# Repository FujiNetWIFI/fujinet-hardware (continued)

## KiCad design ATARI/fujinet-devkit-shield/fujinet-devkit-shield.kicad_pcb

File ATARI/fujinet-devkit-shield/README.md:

# fujinet-devkit-shield

These files are sourced from https://github.com/djtersteegc/fujinet-devkit-shield

This is an alternative hardware platform for [FujiNet](https://fujinet.online/) that allows you to build your own using all through-hole technology (THT) components and an Espressif ESP32-DevKitC-VE devkit board.  You could probably also use a ESP32-DevKitC-VIE board, but you will need to either use an external IPEX connected antenna or engage in some micro soldering since the on-board PCB antenna is not connected by default. You must use ESP32-WROVER based devkit boards, the cheaper ESP32-WROOM boards lack the PSRAM needed by FujiNet code these days. 

The PCB is designed for flexibility in building, with different cabling options and headers for the buttons and LEDs if you want to mount this in your own enclosure. Most components are "jelly bean" parts you may already have or can be purchased for one or two cents in quantity from the usual China based suppliers.  Total cost of the build should be around $20, depending on where you source your parts.  Please see the assembly page for more details.

[Hardware Component Choices and Assembly](https://djtersteegc.github.io/fujinet-devkit-shield/assembly.html)

An interactive BOM and parts placement diagram is also available.

[Interactive Bill of Materials (BOM)](https://djtersteegc.github.io/fujinet-devkit-shield/ibom.html)

Currently this board is not supported by the FujiNet updater app so you will need to use Platform IO to build and upload your own binaries.  Build with the 8MB flash target since the devkit boards have half the flash of the 16MB WROVER modules used on the SIO mounted FujiNet designed by [mozzwald](https://github.com/mozzwald).  In normal operation is should not really matter since 6MB in the 16MB version is currently reserved for over the air (OTA) updates and the release build uses a little more than 2MB of flash as of March 2021 so lots of free space still for future development.

[Board bring up for FujiNet Platform.IO code](https://github.com/FujiNetWIFI/fujinet-platformio/wiki/Board-bring-up-for-FujiNet-Platform.IO-code)

STL's and the [DesignSpark Mechanical](https://www.rs-online.com/designspark/mechanical-software) source file for a 3D printable enclosure are in the **enclosure** directory. Assemble with four M3x10mm screws. Make sure to print 3 copies of the button file.

# Getting a Board

If I have extra PCB's, they will be listed on Tindie.

[https://www.tindie.com/products/tersteeg/fujinet-devkit-shield/](https://www.tindie.com/products/tersteeg/fujinet-devkit-shield/)

Otherwise you can download the Gerbers and use your favorite fab (JLCPCB, PCBWay, etc.) to make your own batch.  It's a standard two layer, 1oz copper board with dimensions of 99mm x 56mm so it squeaks under the 100mm x 100mm limit of the cheap Chinese fabs.

# Hardware Revisions

### Version 1.0

Mostly tested. Standard pin header cable with the SMD MicroSD card connector works.  Still waiting for DB15 connectors to test that cable configuration and a 4.7uf ceramic cap for audio in line. Will also build that one with the micro SD breakout board to verify.  External pin headers for the buttons and LEDs are also untested, but should work. Equivalent to version 1.3+ (pull-up resistors on the SIO and SD card lines) of the SIO port mounted FujiNet.

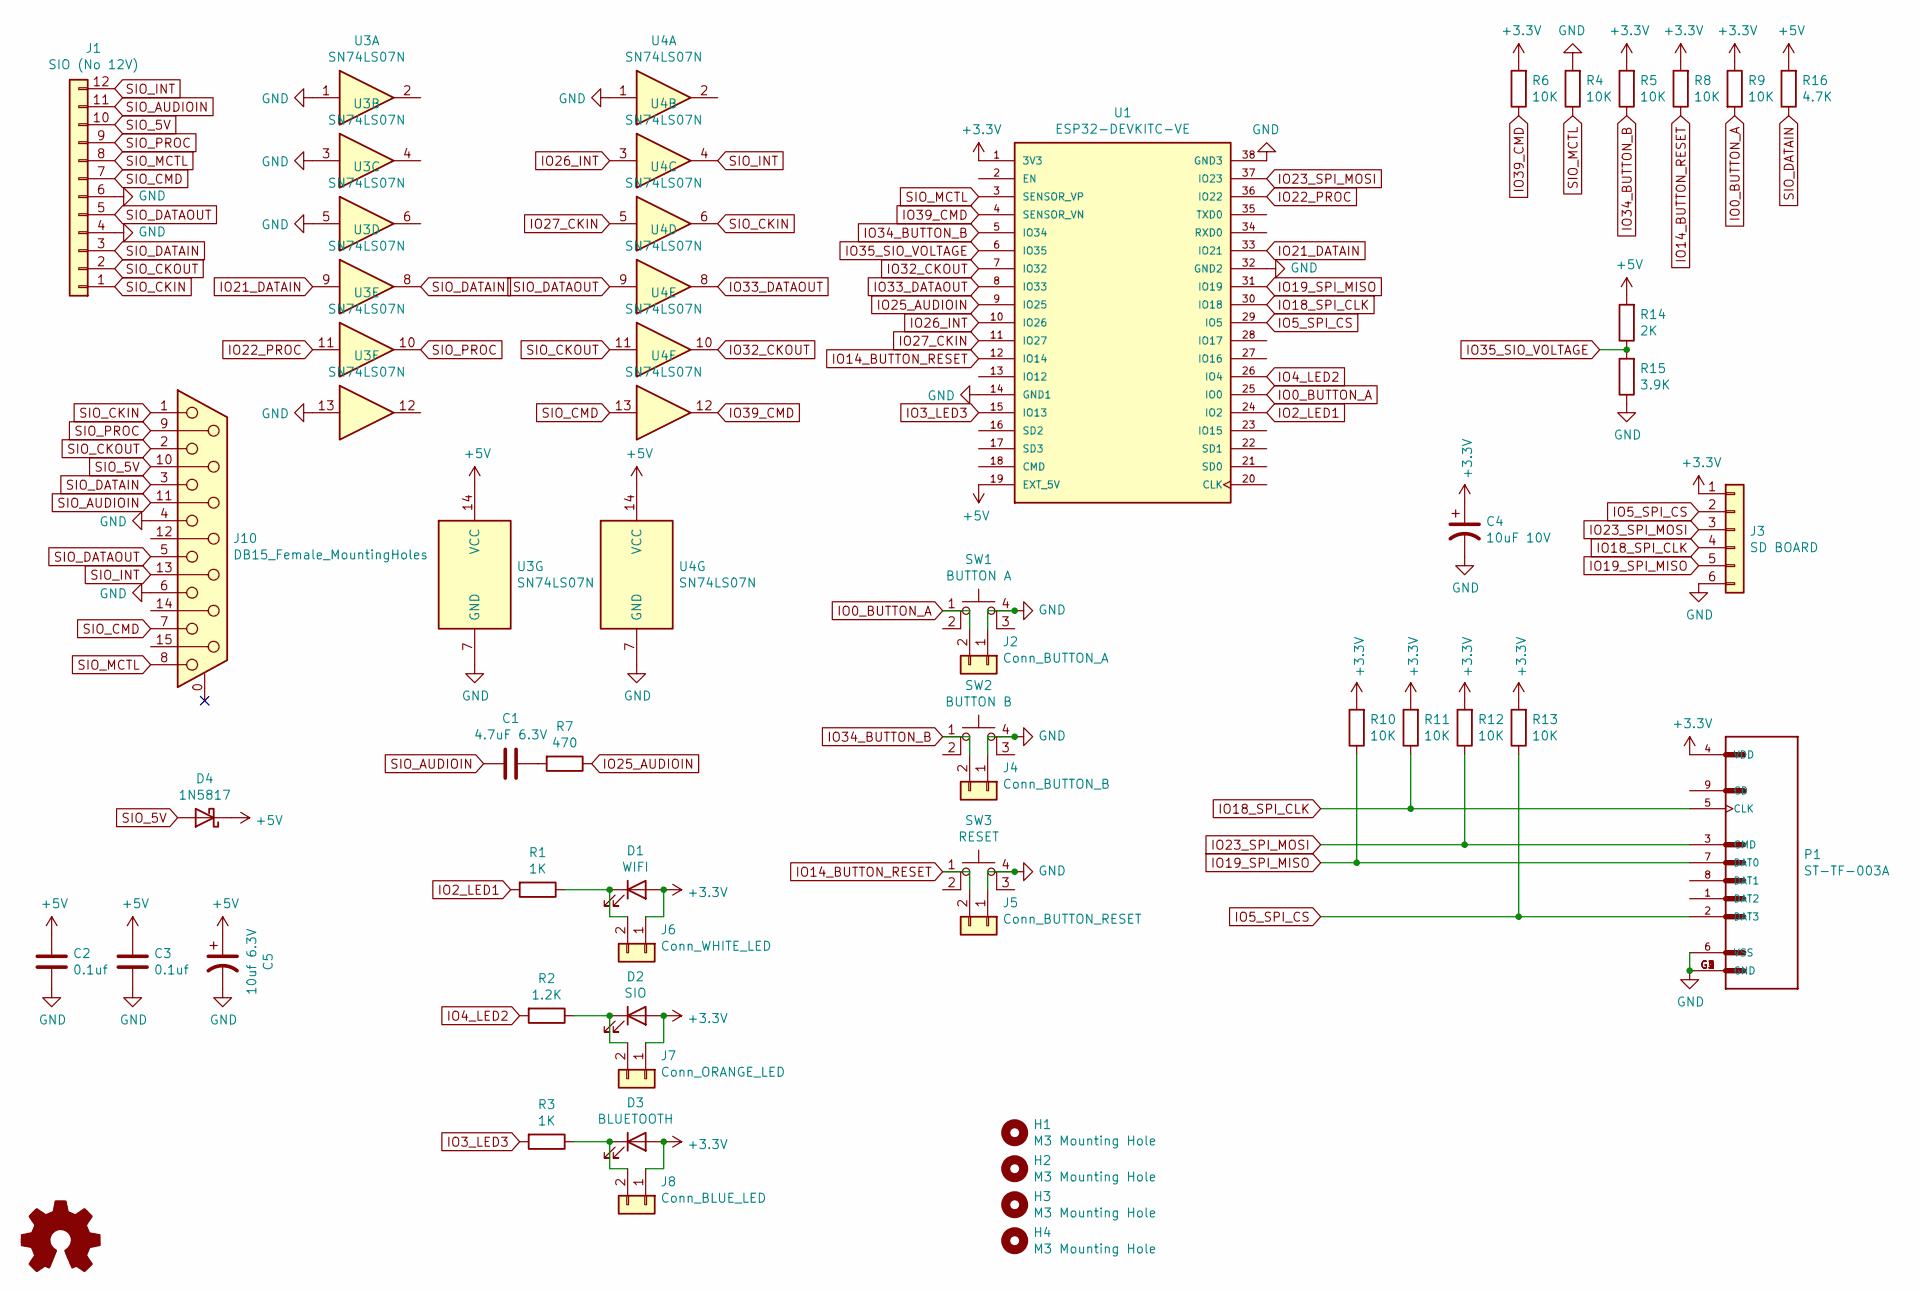
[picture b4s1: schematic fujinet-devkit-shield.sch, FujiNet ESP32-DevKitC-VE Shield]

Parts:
C1: 4.7uF 6.3V; C_Disc_D5.1mm_W3.2mm_P5.00mm
C2, C3: 0.1uf; C_Disc_D5.0mm_W2.5mm_P5.00mm
C4: 10uF 10V; CP_Radial_Tantal_D5.5mm_P5.00mm
C5: 10uf 6.3V; CP_Radial_D6.3mm_P2.50mm
D1: WIFI; LED_D5.0mm
D2: SIO; LED_D5.0mm
D3: BLUETOOTH; LED_D5.0mm
D4: 1N5817; D_DO-41_SOD81_P10.16mm_Horizontal
H1, H2, H3, H4: M3 Mounting Hole; MountingHole_3.2mm_M3
J1: SIO (No 12V); PinHeader_1x12_P2.54mm_Vertical
J2: Conn_BUTTON_A; PinHeader_1x02_P2.54mm_Vertical
J3: SD BOARD; PinHeader_1x06_P2.54mm_Vertical
J4: Conn_BUTTON_B; PinHeader_1x02_P2.54mm_Vertical
J5: Conn_BUTTON_RESET; PinHeader_1x02_P2.54mm_Vertical
J6: Conn_WHITE_LED; PinHeader_1x02_P2.54mm_Vertical
J7: Conn_ORANGE_LED; PinHeader_1x02_P2.54mm_Vertical
J8: Conn_BLUE_LED; PinHeader_1x02_P2.54mm_Vertical
J10: DB15_Female_MountingHoles; DSUB-15_Female_Horizontal_P2.77x2.84mm_EdgePinOffset4.94mm_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
P1: ST-TF-003A; SUNTECH_ST-TF-003A
R1, R3: 1K; R_Axial_DIN0207_L6.3mm_D2.5mm_P7.62mm_Horizontal
R2: 1.2K; R_Axial_DIN0207_L6.3mm_D2.5mm_P7.62mm_Horizontal
R4, R5, R6, R8, R9, R10, R11, R12, R13: 10K; R_Axial_DIN0207_L6.3mm_D2.5mm_P7.62mm_Horizontal
R7: 470; R_Axial_DIN0207_L6.3mm_D2.5mm_P7.62mm_Horizontal
R14: 2K; R_Axial_DIN0207_L6.3mm_D2.5mm_P7.62mm_Horizontal
R15: 3.9K; R_Axial_DIN0207_L6.3mm_D2.5mm_P7.62mm_Horizontal
R16: 4.7K; R_Axial_DIN0207_L6.3mm_D2.5mm_P7.62mm_Horizontal
SW1: BUTTON A; SW_TH_Tactile_Omron_B3F-10xx
SW2: BUTTON B; SW_TH_Tactile_Omron_B3F-10xx
SW3: RESET; SW_TH_Tactile_Omron_B3F-10xx
U1: ESP32-DEVKITC-VE; MODULE_ESP32-DEVKITC-32U; PARTREV N/A
U3, U4: SN74LS07N; DIP-14_W7.62mm_Socket_LongPads

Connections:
+3V3: C4.1, D1.2 (A), D2.2 (A), D3.2 (A), J3.1, J6.1, J7.1, J8.1, P1.4 (VDD), R5.2, R6.2, R8.2, R9.1, R10.2, R11.2, R12.2, R13.2, U1.1 (3V3)
+5V: C2.1, C3.1, C5.1, D4.1 (K), R14.2, R16.2, U1.19 (EXT_5V), U3.14 (VCC), U4.14 (VCC)
GND: C2.2, C3.2, C4.2, C5.2, J1.4, J1.6, J2.1, J3.6, J4.1, J5.1, J10.4, J10.6, P1.6 (VSS), P1.G1 (GND), P1.G2 (GND), P1.G3 (GND), P1.G4 (GND), R4.2, R15.1, SW1.4 (A), SW2.4 (A), SW3.4 (A), U1.14 (GND1), U1.32 (GND2), U1.38 (GND3), U3.1, U3.3, U3.5, U3.7 (GND), U3.13, U4.1, U4.7 (GND)
IO0_BUTTON_A: J2.2, R9.2, SW1.1, U1.25 (IO0)
IO2_LED1: R1.2, U1.24 (IO2)
IO3_LED3: R3.2, U1.15 (IO13)
IO4_LED2: R2.2, U1.26 (IO4)
IO5_SPI_CS: J3.2, P1.2 (DAT3), R13.1, U1.29 (IO5)
IO14_BUTTON_RESET: J5.2, R8.1, SW3.1, U1.12 (IO14)
IO18_SPI_CLK: J3.4, P1.5 (CLK), R11.1, U1.30 (IO18)
IO19_SPI_MISO: J3.5, P1.7 (DAT0), R10.1, U1.31 (IO19)
IO21_DATAIN: U1.33 (IO21), U3.9
IO22_PROC: U1.36 (IO22), U3.11
IO23_SPI_MOSI: J3.3, P1.3 (CMD), R12.1, U1.37 (IO23)
IO25_AUDIOIN: R7.1, U1.9 (IO25)
IO26_INT: U1.10 (IO26), U4.3
IO27_CKIN: U1.11 (IO27), U4.5
IO32_CKOUT: U1.7 (IO32), U4.10
IO33_DATAOUT: U1.8 (IO33), U4.8
IO34_BUTTON_B: J4.2, R5.1, SW2.1, U1.5 (IO34)
IO35_SIO_VOLTAGE: R14.1, R15.2, U1.6 (IO35)
IO39_CMD: R6.1, U1.4 (SENSOR_VN), U4.12
unnamed: C1.2, R7.2
unnamed: D1.1 (K), J6.2, R1.1
unnamed: D2.1 (K), J7.2, R2.1
unnamed: D3.1 (K), J8.2, R3.1
SIO_5V: D4.2 (A), J1.10, J10.10
SIO_AUDIOIN: C1.1, J1.11, J10.11 (P111)
SIO_CKIN: J1.1, J10.1, U4.6
SIO_CKOUT: J1.2, J10.2, U4.11
SIO_CMD: J1.7, J10.7, U4.13
SIO_DATAIN: J1.3, J10.3, R16.1, U3.8
SIO_DATAOUT: J1.5, J10.5, U4.9
SIO_INT: J1.12, J10.13, U4.4
SIO_MCTL: J1.8, J10.8, R4.1, U1.3 (SENSOR_VP)
SIO_PROC: J1.9, J10.9, U3.10

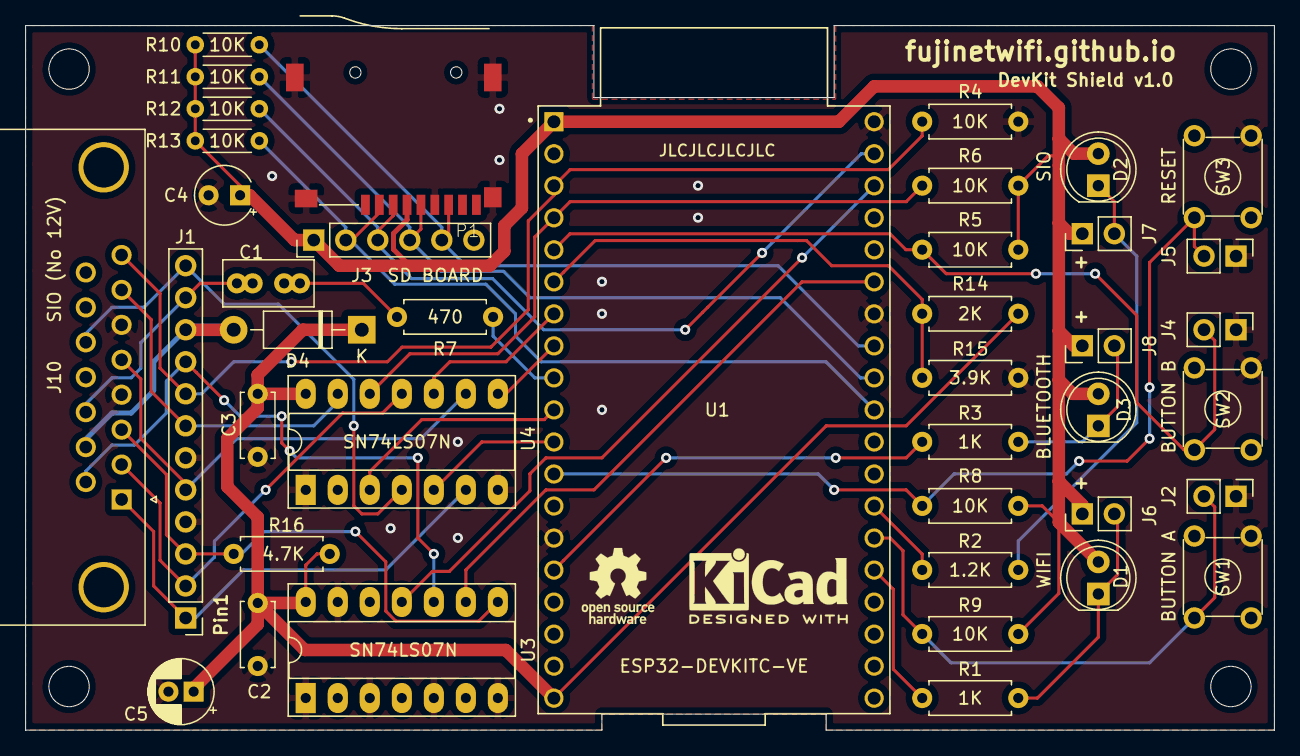
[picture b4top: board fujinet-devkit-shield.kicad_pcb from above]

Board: 2 copper layers, 99.1 x 55.9 mm, 45 parts (0 on the bottom side), 36 nets.

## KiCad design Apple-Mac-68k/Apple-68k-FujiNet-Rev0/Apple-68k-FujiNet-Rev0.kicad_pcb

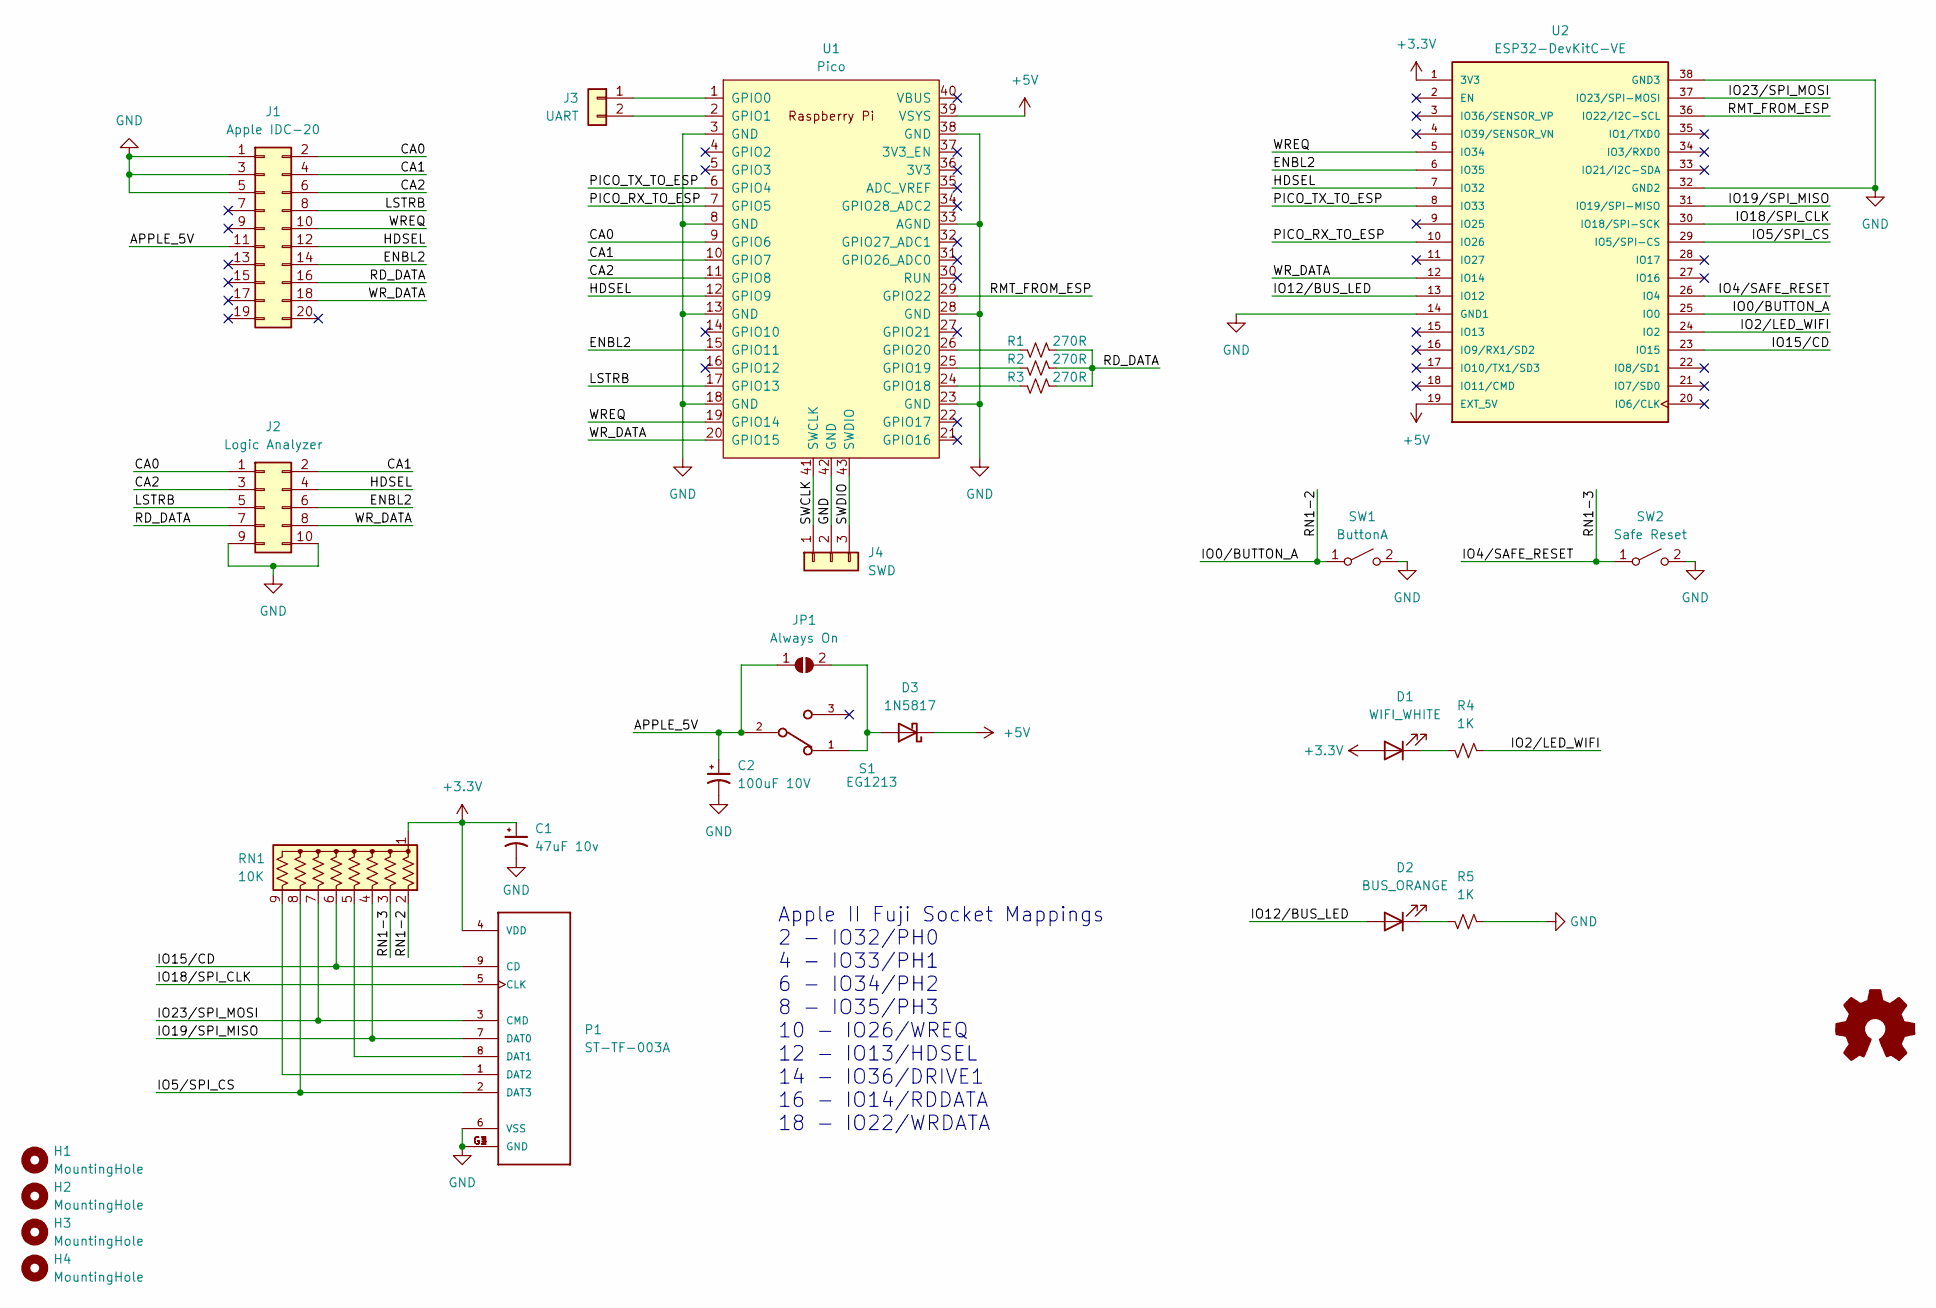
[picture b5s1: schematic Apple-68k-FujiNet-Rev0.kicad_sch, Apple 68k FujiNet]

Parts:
C1: 47uF 10v; CP_EIA-3528-15_AVX-H_Pad1.50x2.35mm_HandSolder
C2: 100uF 10V; CP_Radial_D6.3mm_P2.50mm
D1: WIFI_WHITE; LED_D5.0mm
D2: BUS_ORANGE; LED_D5.0mm
D3: 1N5817; D_DO-41_SOD81_P10.16mm_Horizontal
H1, H2, H3, H4: MountingHole; MountingHole_3.2mm_M3
J1: Apple IDC-20; IDC-Header_2x10_P2.54mm_Horizontal
J2: Logic Analyzer; PinHeader_2x05_P2.54mm_Vertical
J3: UART; PinHeader_1x02_P2.54mm_Vertical
J4: SWD; PinHeader_1x03_P2.54mm_Vertical
JP1: Always On; SolderJumper-2_P1.3mm_Open_RoundedPad1.0x1.5mm
P1: ST-TF-003A; SUNTECH_ST-TF-003A
R1, R2, R3: 270R; R_Axial_DIN0207_L6.3mm_D2.5mm_P7.62mm_Horizontal
R4, R5: 1K; R_Axial_DIN0207_L6.3mm_D2.5mm_P7.62mm_Horizontal
RN1: 10K; R_Array_SIP9
S1: EG1213; SW_EG1213
SW1: ButtonA; SW_PUSH_6mm_H5mm
SW2: Safe Reset; SW_PUSH_6mm_H5mm
U1: Pico; RPi_Pico_THT
U2: ESP32-DevKitC-VE; MODULE_ESP32-DEVKITC-32U; PARTREV N/A

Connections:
+3.3V: C1.1, D1.2 (A), P1.4 (VDD), RN1.1 (common), U2.1 (3V3)
+5V: D3.1 (K), U1.39 (VSYS), U2.19 (EXT_5V)
/APPLE_5V: C2.1, J1.11, JP1.1 (A), S1.2
/CA0: J1.2, J2.1, U1.9 (GPIO6)
/CA1: J1.4, J2.2, U1.10 (GPIO7)
/CA2: J1.6, J2.3, U1.11 (GPIO8)
/ENBL2: J1.14, J2.6, U1.15 (GPIO11), U2.6 (IO35)
/HDSEL: J1.12, J2.4, U1.12 (GPIO9), U2.7 (IO32)
/IO0/BUTTON_A: RN1.2 (R1), SW1.1 (A), U2.25 (IO0)
/IO2/LED_WIFI: R4.2, U2.24 (IO2)
/IO4/SAFE_RESET: RN1.3 (R2), SW2.1 (A), U2.26 (IO4)
/IO5/SPI_CS: P1.2 (DAT3), RN1.8 (R7), U2.29 (IO5/SPI-CS)
/IO12/BUS_LED: D2.2 (A), U2.13 (IO12)
/IO15/CD: P1.9 (CD), RN1.6 (R5), U2.23 (IO15)
/IO18/SPI_CLK: P1.5 (CLK), U2.30 (IO18/SPI-SCK)
/IO19/SPI_MISO: P1.7 (DAT0), RN1.4 (R3), U2.31 (IO19/SPI-MISO)
/IO23/SPI_MOSI: P1.3 (CMD), RN1.7 (R6), U2.37 (IO23/SPI-MOSI)
/LSTRB: J1.8, J2.5, U1.17 (GPIO13)
/PICO_RX_TO_ESP: U1.7 (GPIO5), U2.10 (IO26)
/PICO_TX_TO_ESP: U1.6 (GPIO4), U2.8 (IO33)
/RD_DATA: J1.16, J2.7, R1.2, R2.2, R3.2
/RMT_FROM_ESP: U1.29 (GPIO22), U2.36 (IO22/I2C-SCL)
/SWCLK: J4.1, U1.41 (SWCLK)
/SWDIO: J4.3, U1.43 (SWDIO)
/WREQ: J1.10, U1.19 (GPIO14), U2.5 (IO34)
/WR_DATA: J1.18, J2.8, U1.20 (GPIO15), U2.12 (IO14)
GND: C1.2, C2.2, J1.1, J1.3, J1.5, J2.9, J2.10, J4.2, P1.6 (VSS), P1.G1 (GND), P1.G2 (GND), P1.G3 (GND), P1.G4 (GND), R5.2, SW1.2 (B), SW2.2 (B), U1.3 (GND), U1.8 (GND), U1.13 (GND), U1.18 (GND), U1.23 (GND), U1.28 (GND), U1.33 (AGND), U1.38 (GND), U1.42 (GND), U2.14 (GND1), U2.32 (GND2), U2.38 (GND3)
unnamed: D1.1 (K), R4.1
unnamed: D2.1 (K), R5.1
unnamed: D3.2 (A), JP1.2 (B), S1.1
unnamed: J3.1, U1.1 (GPIO0)
unnamed: J3.2, U1.2 (GPIO1)
unnamed: P1.8 (DAT1), RN1.5 (R4)
unnamed: P1.1 (DAT2), RN1.9 (R8)
unnamed: R3.1, U1.24 (GPIO18)
unnamed: R2.1, U1.25 (GPIO19)
unnamed: R1.1, U1.26 (GPIO20)

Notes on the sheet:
Apple II Fuji Socket Mappings 2 - IO32/PH0 4 - IO33/PH1 6 - IO34/PH2 8 - IO35/PH3 10 - IO26/WREQ 12 - IO13/HDSEL 14 - IO36/DRIVE1 16 - IO14/RDDATA 18 - IO22/WRDATA

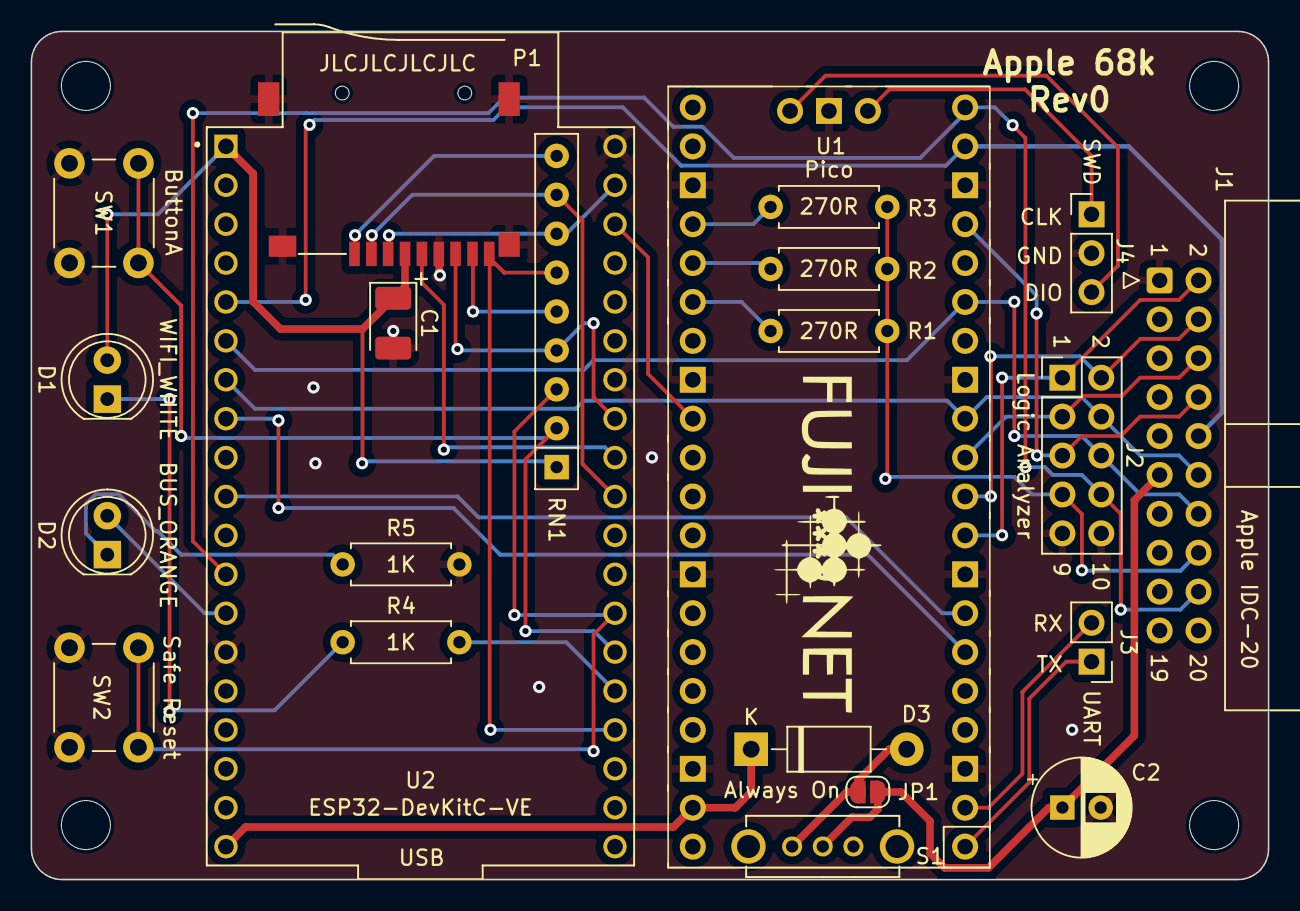
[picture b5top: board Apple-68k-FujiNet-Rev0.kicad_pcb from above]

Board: 2 copper layers, 80.8 x 55.4 mm, 26 parts (0 on the bottom side), 37 nets.

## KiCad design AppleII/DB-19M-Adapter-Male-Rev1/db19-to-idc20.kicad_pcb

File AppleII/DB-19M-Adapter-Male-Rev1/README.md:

A DB19 to IDC-20 adapter for use with Rev1 Devkit FujiApple boards, or Rev0 MacFuji boards.  Uses cheap DB pins originally intended to be soldered on the end of wires and is housed in a 3D printed case.

[Schematic](db19-to-idc20-schematic.pdf)

# BOM

IDC-20 2.54mm 2x10 Male Box Header - https://www.aliexpress.us/item/3256806042421204.html

DB 1.0mm pins, Wires Solder Model - https://www.aliexpress.us/item/3256802431271655.html

M2.5 Nuts - https://www.aliexpress.us/item/2255800799473326.html

M2.5x16mm Countersunk Screws - https://www.aliexpress.us/item/2251832747871730.html

# Case

The case parts are designed to printed at a 0.2mm layer height. There are two different DB19 connector options for the case.

One is a flat back that IMHO looks better but only works on an Apple IIc or IIc+. 

The other is a stepped back that provides the clearance needed to sit flush on a IIgs or compact Mac model.

# Solder Jumpers

**-12V** - Routes -12V to pin 9

**12V** - Routes +12V to pins 13, 15, and 19

**PIN17** - Routes either the Drive2 signal or +12V to pin 17

# Assembly

First solder on the IDC-20 connector with the keying notch matched to the silkscreen.

**If using with a Rev1 FujiApple close the PIN17 solder jumper to Drive2.**

Cleanup you 3D printed DB19 connector by using a 1mm and 2mm drill bit to size the DB pin holes.

Press some M2.5 nuts into the DB19 connector, place it on a female DB19, or cut down female DB25, connector and then insert the 19 DB pins with the tube cut facing outwards to enable easier soldering access.

Then slide the PCB into the case and work it over the DB pins.  I like to temporarily screw the PCB/case to the DB19 connector with some M2.5x10mm nylon screws (they have a very small head) and clamp the whole assembly in a vise for soldering.  The ends of the tube cuts in the DB19 pins should be flush with the top of the PCB.

Finally assemble the case lid with two M2.5x16mm screws.

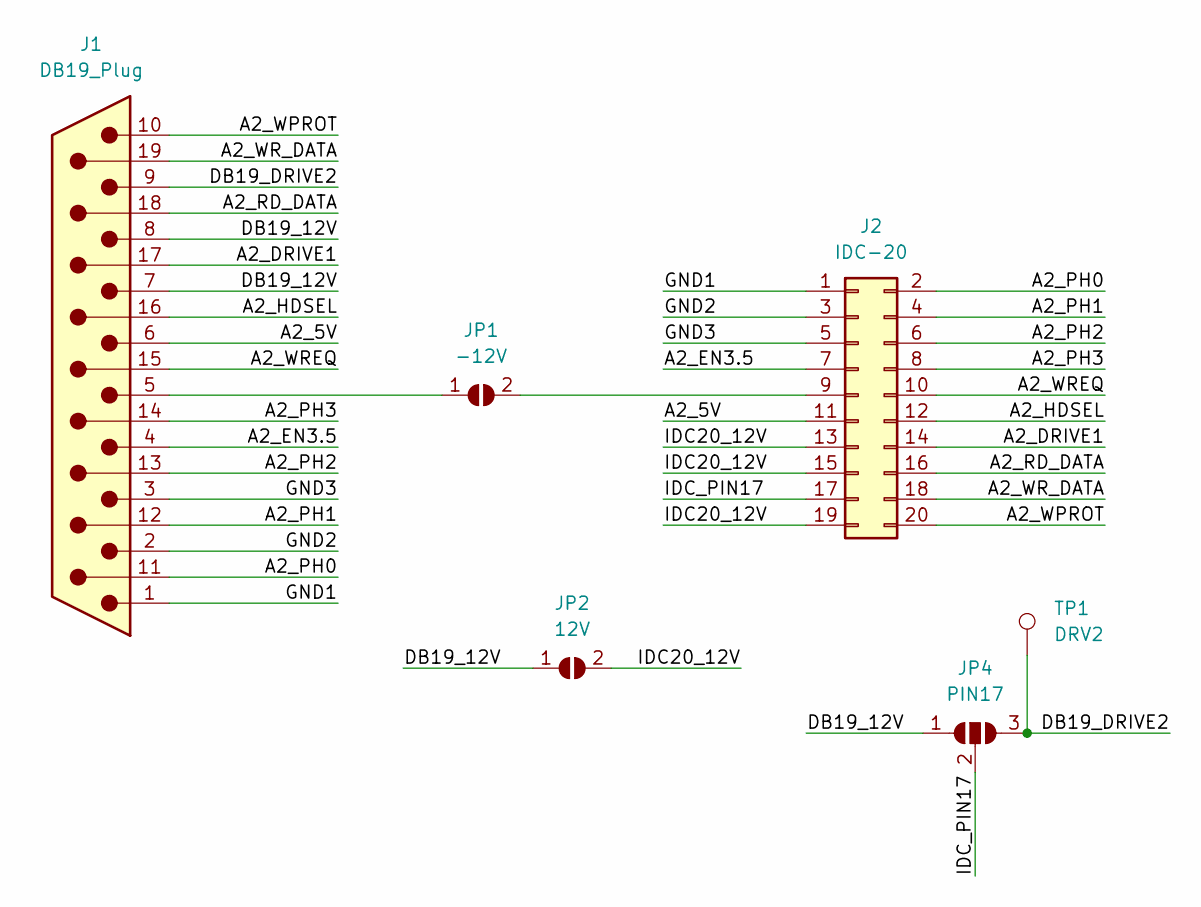
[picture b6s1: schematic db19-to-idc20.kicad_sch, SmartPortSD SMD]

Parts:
J1: DB19_Plug; DSUB-19_Male_Vertical_P2.77x2.84mm_Narrow_MountingHoles_Ful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
J2: IDC-20; IDC-Header_2x10_P2.54mm_Vertical
JP1: -12V; SolderJumper-2_P1.3mm_Open_RoundedPad1.0x1.5mm
JP2: 12V; SolderJumper-2_P1.3mm_Open_RoundedPad1.0x1.5mm
JP4: PIN17; SolderJumper-3_P1.3mm_Open_RoundedPad1.0x1.5mm_NumberLabels
TP1: DRV2; TestPoint_Pad_D1.5mm

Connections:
/A2_5V: J1.6, J2.11
/A2_DRIVE1: J1.17, J2.14
/A2_EN3.5: J1.4, J2.7
/A2_HDSEL: J1.16, J2.12
/A2_PH0: J1.11, J2.2
/A2_PH1: J1.12, J2.4
/A2_PH2: J1.13, J2.6
/A2_PH3: J1.14, J2.8
/A2_RD_DATA: J1.18, J2.16
/A2_WPROT: J1.10, J2.20
/A2_WREQ: J1.15, J2.10
/A2_WR_DATA: J1.19, J2.18
/DB19_12V: J1.7, J1.8, JP2.1 (A), JP4.1 (A)
/DB19_DRIVE2: J1.9, JP4.3 (B), TP1.1
/GND1: J1.1, J2.1
/GND2: J1.2, J2.3
/GND3: J1.3, J2.5
/IDC20_12V: J2.13, J2.15, J2.19, JP2.2 (B)
/IDC_PIN17: J2.17, JP4.2 (C)
unnamed: J2.9, JP1.2 (B)
unnamed: J1.5, JP1.1 (A)

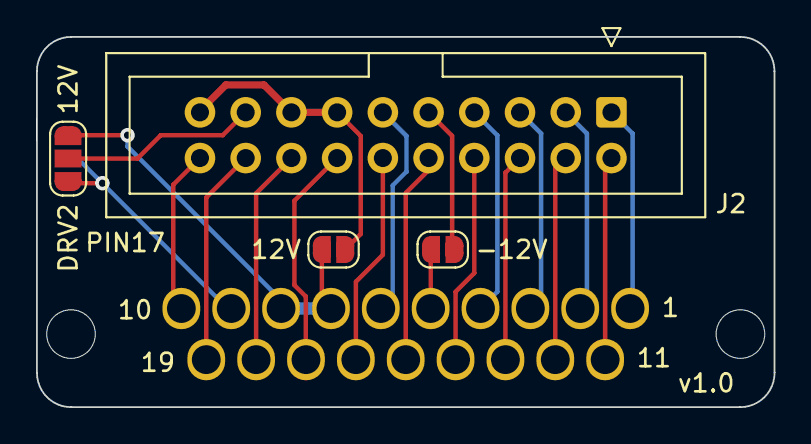
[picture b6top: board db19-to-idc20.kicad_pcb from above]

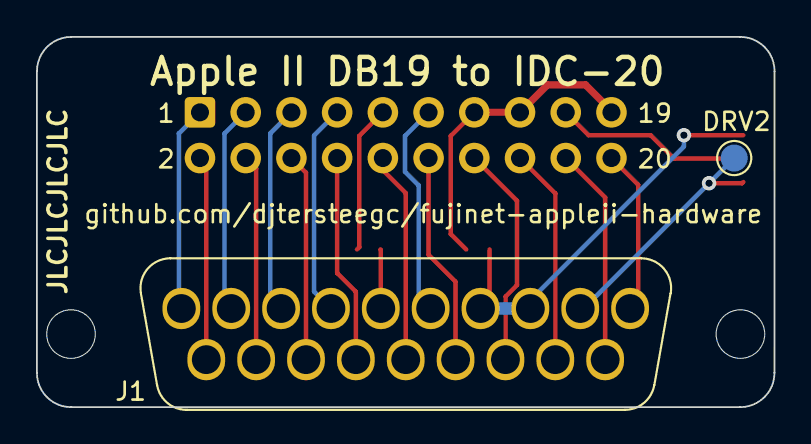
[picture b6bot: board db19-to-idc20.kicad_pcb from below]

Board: 2 copper layers, 41.0 x 20.6 mm, 6 parts (2 on the bottom side), 21 nets.

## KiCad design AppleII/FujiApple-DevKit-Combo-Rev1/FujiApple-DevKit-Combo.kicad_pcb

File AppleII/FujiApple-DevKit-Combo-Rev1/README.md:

This is built primary to work in DB19 mode, but can also be used with the DB19 Male Adapter to plug into a IDC-20 disk card. I tend to build them in the short configuration to keep the case height as slim as possible when plugged in the Apple II. The downside of this is once you solder the ESP32 to the board, you will not be able to access the components under it for troubleshooting.

[Schematic](https://djtersteegc.github.io/fujinet-hardware/AppleII/Schematic-DevKit-Combo-v1.0.pdf)

# BOM

There's an interactive BOM [here](https://djtersteegc.github.io/fujinet-hardware/AppleII/ibom-DevKit-Combo-v1.0.html), and CSV version with footprint info [here](https://djtersteegc.github.io/fujinet-hardware/AppleII/bom-DevKit-Combo-v1.0.csv). The interactive one is super useful when placing the SMD components.

The DB19 connector uses 16 of the wire solder style pins from this seller on AliExpress - https://www.aliexpress.us/item/3256802431271655.html

If building in the tall configuration you will also need two 19p 2.54mm female header strips. I buy the the [40p versions](https://www.aliexpress.us/item/3256805857141565.html) and cut them down to size.

Make sure to buy the ESP32-DEVKITC-VE version of the devkit board.  If you are in the US, [Amazon](https://www.amazon.com/gp/product/B087TNPQCV) is a great place to pick one of these up with Prime shipping.

The MicroSD sockets are readily available from [AliExpress](https://www.aliexpress.us/item/3256802476596462.html), [Amazon](https://www.amazon.com/Spring-Loaded-Transflash-Memory-Socket/dp/B0CDC5Q1HF), eBay and other places, sometimes called _Push Push TransFlash Socket_.

The "standard" FujiNet LED's colors are white for Wifi and orange for bus activity.

The case requires two M2.5x16mm countersunk screws and two M2.5 hex nuts.

Buying everything in quantity 10 from someplace like AliExpress will be much cheaper, especially if you plan on doing multiple builds. But here's a Mouser shared project that includes everything but the DB19 connector pins -  https://www.mouser.com/ProjectManager/ProjectDetail.aspx?AccessID=C40F378B5C

# Case

Designed to be printed at a 0.2mm layer height. Use Polymaker PolyTerra Matte PLA in Muted White (Hex Code: #Bfbcb1) for a good match to Apple Platinum.

There are two rectangular lightpipes to be printed in clear filament. If you find the standard one fits to losely in the opening, print a pair of the "tight" versions which a slightly bigger.

Assemble with two M2.5x16mm countersunk screws and two M2.5 hex nuts.

# Assembly

Solder on all the SMD components.  I use solder paste hand applied with a pneumatic dispenser and then finish on a hot plate. But you can also hand solder, use hot air, or even order a stencil for paste application and use a proper reflow oven.

If building in the short configuration, double check all your solder joints on the MicroSD socket and buffers since once you solder on the ESP32, you will lose access to the all the components under it.

Next solder on the IDC-20 connector.

Before mounting the ESP32, you will need to solder on the DB19 pins.  Some of these pics are from the DB19 adapter build, but the process is the same.

Cleanup you 3D printed DB19 connector by using a 1mm and 2mm drill bit to size the DB pin holes.

Press some M2.5 nuts into the DB19 connector, place it on a female DB19, or cut down female DB25, connector and then insert the 19 DB pins with the tube cut facing forward away from the IDC-20 connector to enable easier soldering access.

Then slide the PCB into the case and work it over the DB pins.  I like to temporarily screw the PCB/case to the DB19 connector with some M2.5x10mm nylon screws (they have a very small head) and clamp the whole assembly in a vise for soldering.  The ends of the tube cuts in the DB19 pins should be flush with the top of the PCB.

Now you can solder on the ESP32.  Once complete you will need to trim the pins to allow the PCB to slide back in the case.

Insert the two lightpipes with the lip facing up, slide the PCB under them, and then secure the case lid with two M2.5x16mm screws.

# Flashing

Use the standard Apple II firmware in the [FujiNet Flasher](https://fujinet.online/download/)

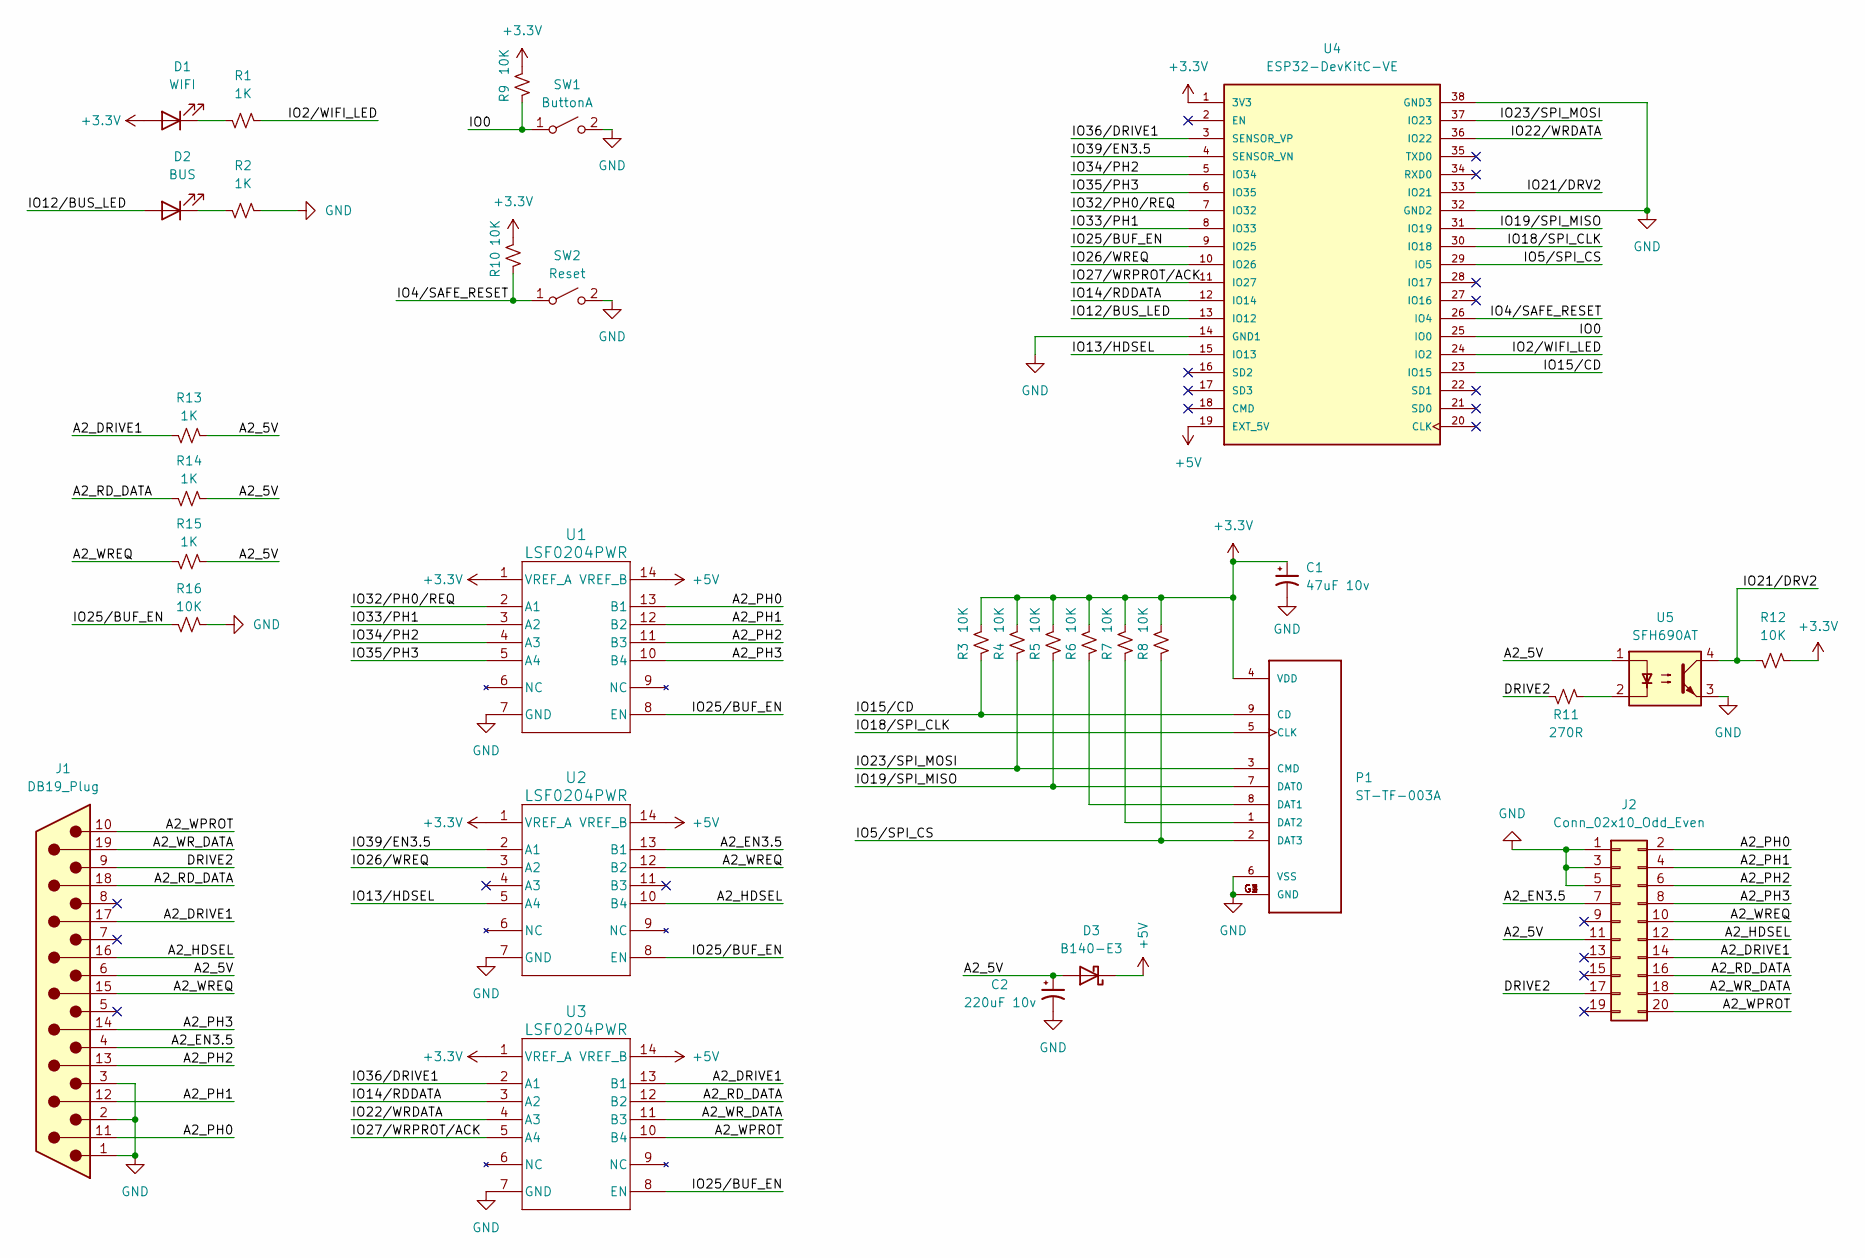
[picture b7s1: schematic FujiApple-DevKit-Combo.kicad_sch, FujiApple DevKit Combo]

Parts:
C1: 47uF 10v; CP_EIA-3528-15_AVX-H_Pad1.50x2.35mm_HandSolder
C2: 220uF 10v; CP_EIA-7343-30_AVX-N_Pad2.25x2.55mm_HandSolder
D1: WIFI; 1204 Side Emitting LED
D2: BUS; 1204 Side Emitting LED
D3: B140-E3; D_SMA
J1: DB19_Plug; DSUB-19_Male_Vertical_P2.77x2.84mm_Narrow_MountingHoles_Ful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
J2: Conn_02x10_Odd_Even; IDC-Header_2x10_P2.54mm_Vertical
P1: ST-TF-003A; SUNTECH_ST-TF-003A
R1, R2, R13, R14, R15: 1K; R_0805_2012Metric_Pad1.20x1.40mm_HandSolder
R3, R4, R5, R6, R7, R8, R9, R10, R12, R16: 10K; R_0805_2012Metric_Pad1.20x1.40mm_HandSolder
R11: 270R; R_0805_2012Metric_Pad1.20x1.40mm_HandSolder
SW1: ButtonA; SW_Push_SPST_NO_Alps_SKRK
SW2: Reset; SW_Push_SPST_NO_Alps_SKRK
U1, U2, U3: LSF0204PWR; TSSOP-14_4.4x5mm_P0.65mm
U4: ESP32-DevKitC-VE; MODULE_ESP32-DEVKITC-32U; PARTREV N/A
U5: SFH690AT; SO-4_4.4x3.9mm_P2.54mm

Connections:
+3.3V: C1.1, D1.2 (A), P1.4 (VDD), R3.2, R4.2, R5.2, R6.2, R7.2, R8.2, R9.2, R10.2, R12.2, U1.1 (VREF_A), U2.1 (VREF_A), U3.1 (VREF_A), U4.1 (3V3)
+5V: D3.1 (K), U1.14 (VREF_B), U2.14 (VREF_B), U3.14 (VREF_B), U4.19 (EXT_5V)
/A2_5V: C2.1, D3.2 (A), J1.6, J2.11, R13.2, R14.2, R15.2, U5.1
/A2_DRIVE1: J1.17, J2.14, R13.1, U3.13 (B1)
/A2_EN3.5: J1.4, J2.7, U2.13 (B1)
/A2_HDSEL: J1.16, J2.12, U2.10 (B4)
/A2_PH0: J1.11, J2.2, U1.13 (B1)
/A2_PH1: J1.12, J2.4, U1.12 (B2)
/A2_PH2: J1.13, J2.6, U1.11 (B3)
/A2_PH3: J1.14, J2.8, U1.10 (B4)
/A2_RD_DATA: J1.18, J2.16, R14.1, U3.12 (B2)
/A2_WPROT: J1.10, J2.20, U3.10 (B4)
/A2_WREQ: J1.15, J2.10, R15.1, U2.12 (B2)
/A2_WR_DATA: J1.19, J2.18, U3.11 (B3)
/DRIVE2: J1.9, J2.17, R11.1
/IO0: R9.1, SW1.1 (A), U4.25 (IO0)
/IO2/WIFI_LED: R1.2, U4.24 (IO2)
/IO4/SAFE_RESET: R10.1, SW2.1 (A), U4.26 (IO4)
/IO5/SPI_CS: P1.2 (DAT3), R8.1, U4.29 (IO5)
/IO12/BUS_LED: D2.2 (A), U4.13 (IO12)
/IO13/HDSEL: U2.5 (A4), U4.15 (IO13)
/IO14/RDDATA: U3.3 (A2), U4.12 (IO14)
/IO15/CD: P1.9 (CD), R3.1, U4.23 (IO15)
/IO18/SPI_CLK: P1.5 (CLK), U4.30 (IO18)
/IO19/SPI_MISO: P1.7 (DAT0), R5.1, U4.31 (IO19)
/IO21/DRV2: R12.1, U4.33 (IO21), U5.4
/IO22/WRDATA: U3.4 (A3), U4.36 (IO22)
/IO23/SPI_MOSI: P1.3 (CMD), R4.1, U4.37 (IO23)
/IO25/BUF_EN: R16.1, U1.8 (EN), U2.8 (EN), U3.8 (EN), U4.9 (IO25)
/IO26/WREQ: U2.3 (A2), U4.10 (IO26)
/IO27/WRPROT/ACK: U3.5 (A4), U4.11 (IO27)
/IO32/PH0/REQ: U1.2 (A1), U4.7 (IO32)
/IO33/PH1: U1.3 (A2), U4.8 (IO33)
/IO34/PH2: U1.4 (A3), U4.5 (IO34)
/IO35/PH3: U1.5 (A4), U4.6 (IO35)
/IO36/DRIVE1: U3.2 (A1), U4.3 (SENSOR_VP)
/IO39/EN3.5: U2.2 (A1), U4.4 (SENSOR_VN)
GND: C1.2, C2.2, J1.1, J1.2, J1.3, J2.1, J2.3, J2.5, P1.6 (VSS), P1.G1 (GND), P1.G2 (GND), P1.G3 (GND), P1.G4 (GND), R2.2, R16.2, SW1.2 (B), SW2.2 (B), U1.7 (GND), U2.7 (GND), U3.7 (GND), U4.14 (GND1), U4.32 (GND2), U4.38 (GND3), U5.3
unnamed: D1.1 (K), R1.1
unnamed: D2.1 (K), R2.1
unnamed: P1.8 (DAT1), R6.1
unnamed: P1.1 (DAT2), R7.1
unnamed: R11.2, U5.2

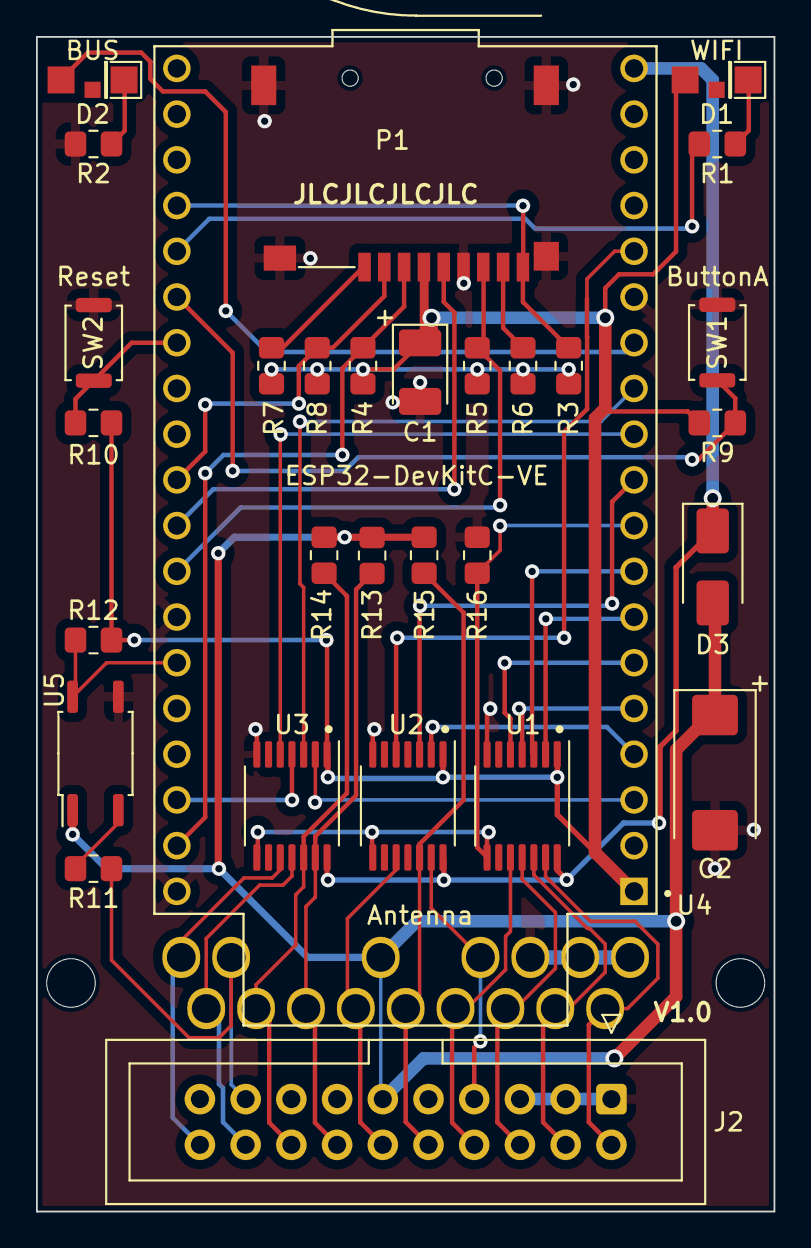
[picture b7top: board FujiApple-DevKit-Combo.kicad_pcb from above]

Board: 2 copper layers, 41.0 x 65.3 mm, 31 parts (1 on the bottom side), 43 nets.
